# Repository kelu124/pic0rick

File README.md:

# the _pic0rick_ project

The pic0rick is a very central board for an ultrasound pulse-echo system. It is composed of a main board, based on the RP2040 (or RP2350) and easy to solder SMD, to which a single, and a double PMOD connector can connect to addons:

* The main board is equipped with a 60Msps, 10bit ADC. Front end is protected against high-voltage pulses, and features a proven time-gain compensation system consisting in a AD8331 (7.5 dB to 55.5dB) with a controlling (MCP4812) SPI DAC.
* The single PMOD connector can plug to the Pulser board, which can be equipped with a simple +-25V generation board. Together, they generate the pulse on behalf of the pic0rick main board. The setup can generate three-level pulses ( with a pair of MD1210 + TC6320 ).
* The double PMOD connector can be used for virtually anything. The current code allows for a VGA to be connected, which displays acquisitions from the board.

The current system uses both PIOs (one for the acquisition, the other for the VGA) which leaves the other resources of the rp2040 relatively free to use for your own priorities.

Published documents include:
* KiCad design files for the main board
* KiCad design files for the pulser + hv boards
* KiCad design files for the MUX
* KiCad design files for other boards =)
* rp2040/rp2350 firmware for the microcontroller.

I _know_ the PMODs aren't strictly speaking PMODs, I needed to have 5V facility on the header =)

And if you want to discuss the project - [meet us on our chat](https://matrix.to/#/!dEbJSiragnEvzVBdUa:matrix.org?via=matrix.org).

# Repository layout

| Path | Contents |
|------|----------|
| `firmware/` | The unified RP2040/RP2350 firmware (CMake project `adc-pulse`). One source tree with `-DMUX` / `-DDSP` build options. `hw/` = shared acquisition + pulser + spi1 DAC; `dsp/` = RP2350 DSP (CMSIS-DSP Hilbert envelope + binary protocol); `max/` = MAX14866 mux. `version.yaml` + `CHANGELOG.md` track the firmware version; `build.sh` builds all 6 variants into `dist/`. |
| `python/` | Host stack (`pic0rick` package): `device.py` (serial driver), `dsp.py` (binary frame protocol), `ndt_acquisition.py` (echo/thickness analysis + HDF5), and the `example_*.ipynb` notebooks. |
| `hardware/` | KiCad design files and `build.sh` fabrication outputs — main board (`adc/`), pulser + HV (`pulser/`), MUX (`mux/`), VGA (`vga/`), PSRAM (`psram/`). |
| `docs/` | Documentation: `dsp_output_formats.md`, `dsp_test_guide.md`, `images/`, `data/`, `fw_history/` (maintainer-curated reference `.uf2` baselines), and `claude/` (cross-session engineering notes). |
| `.github/workflows/` | CI: builds all firmware variants and publishes a release on push to `main`. |

# Getting Started

## Prerequisites

* pic0rick main board + pulser board + HV board (assembled)
* USB-C cable
* Python 3.9+
* A piezoelectric transducer (e.g. 5 MHz single-element contact probe)

## Building the firmware

The firmware is a single source tree (`firmware/`) with build options:

- **`-DMUX`** (default on) — MAX14866 HV multiplexer support.
- **`-DDSP`** (RP2350/`pico2` only) — on-board Hilbert-envelope DSP + binary
  protocol (see [DSP build](#dsp-build-rp2350) below).

```bash
cd firmware && ./build.sh          # builds all 6 variants into firmware/dist/:
#   rp2040-{mux,nomux}, rp2350-{mux,nomux}, rp2350-{mux,nomux}-dsp
```

Prebuilt `firmware/rp2040.uf2` / `firmware/rp2350.uf2` are the default (mux,
non-DSP) builds. CI publishes all variants as release assets.

## Flashing the firmware

1. Hold the **BOOTSEL** button on the RP2040/RP2350 while connecting USB — the board mounts as a USB mass-storage device. *(After the first flash you can instead send the `reboot-dfu` command over serial to re-enter the bootloader without the button.)*
2. Copy the compiled `.uf2` file into the drive. The board reboots automatically.
3. Verify: open a serial terminal at 115,200 baud. You should see the `run>` prompt (stdio build). Send `version` to confirm the firmware version, board and options.

## Installing the Python library

```bash
pip install pyserial numpy h5py scipy matplotlib
```

Clone this repo and add `python/` to your path, or run notebooks from the `python/` directory.

## Quick start

The examples below target the **DSP build** (`-DDSP`, RP2350) — the recommended
firmware, which streams CRC-checked binary frames. For the plain **stdio build**
see [Serial commands](#serial-commands-stdio--non-dsp-build).

```python
from pic0rick.device import Pic0rick
from pic0rick.ndt_acquisition import UltrasonicAcquisition

probe = Pic0rick()           # auto-detects the USB serial port
print(probe.version()['raw'])

# Set TGC gain (raw DAC value 0–1023; higher = more gain)
probe.set_gain(300)

# Configure and arm the pulser so the capture transmits
probe.configure_pulse(negative_ns=200, damp_ns=2000, positive_ns=200,
                      order="pos-first")
probe.arm_pulser()

frame = probe.read_raw()     # 8000-sample raw ADC frame (CRC-checked)
signal = frame.samples()     # numpy uint16, 0..1023
# envelope = probe.read_fft().samples()   # 4096-sample Hilbert envelope
probe.disarm_pulser()
```

> On the **stdio (non-DSP)** build instead use `probe.dac(gain)`,
> `probe.pulse_adc_trigger(pon, poff, damp)`, `probe.read()`.

Or use the higher-level acquisition wrapper (drives the DSP build for you):

```python
acq = UltrasonicAcquisition.from_probe(
    Fech=60e6,
    pon=70,        # pulse-on duration [ns]
    poff=70,       # pulse-off duration [ns]
    damp=6000,     # damping duration [ns]
    gain=300,      # raw DAC value (0–1023)
    target="1018 steel 25 mm",
    h5_path="my_scan.h5",
)
acq.plot()
```

## Serial commands (stdio / non-DSP build)

The stdio build exposes a text protocol at 115,200 baud (USB CDC), with a `run>`
prompt:

| Command | Arguments | Description |
|---------|-----------|-------------|
| `start acq <pon> <poff> <damp>` | nanoseconds | Fire pulse, DMA-capture 8000 samples |
| `write dac <N>` | 0–1023 | Set TGC gain (MCP4812 10-bit DAC) |
| `read` | — | Return last captured buffer (hex, comma-separated 10-bit values) |
| `write mux <hex>` | hex word | Write the MAX14866 shift register *(MUX builds)* |
| `set mux` / `clear mux` | — | Pulse the MAX14866 SET / CLR line *(MUX builds)* |
| `version` | — | Print firmware version, board/chip, options, git hash, release URL |
| `reboot-dfu` | — | Reboot into the USB bootloader (BOOTSEL) for reflashing |

> The **DSP build** uses different commands (`dac write`, `read_raw`, `read_fft`,
> …) and a binary protocol — see [DSP build](#dsp-build-rp2350).

### Parameter details

**`pon` / `poff` / `damp`** — expressed in **nanoseconds** from Python. The firmware converts them to 125 MHz clock cycles internally (divides by 8).

**`gain`** — raw 10-bit DAC value (0–1023) controlling the VGAIN pin of the AD8331 TGC amplifier (7.5 dB to 55.5 dB range). The example notebook uses values in the 0–500 range.

### DSP build (RP2350)

Building with `-DDSP=ON` (RP2350/`pico2`) adds an on-board DSP path: a float32
CMSIS-DSP Hilbert envelope. Instead of the text REPL it speaks a binary framed
protocol (64-byte header + CRC32) with two capture modes:

- **`read_raw`** — 8000 raw ADC samples (no FFT).
- **`read_fft`** — 4096-sample Hilbert envelope.

plus `acq raw|envelope|alaw`, `stream start|stop`, `dsp scale|selftest`,
`dac write <0..1023>`, `pulse config <neg_ns> <damp_ns> <pos_ns> <neg-first|pos-first>`,
`pulser arm|disarm`, `status`, `help`, `version`, `reboot-dfu`.

Drive it from Python with `pic0rick.dsp` and these `Pic0rick` methods:
`version()`, `status()`, `set_gain(n)`, `configure_pulse(...)`,
`arm_pulser()`/`disarm_pulser()`, `read_raw()`, `read_fft()`, `capture(payload)`.
The frame and status formats are documented in
[`docs/dsp_output_formats.md`](docs/dsp_output_formats.md); see
[`docs/dsp_test_guide.md`](docs/dsp_test_guide.md) and the
`python/example_dsp.ipynb` / `python/example_simple.ipynb` notebooks.

## Signal chain

```
Transducer
   │
   ├──► TX path: PIO pulser GPIO11/12 (P+/P-) + GPIO16/17 (PDAMP/OE) → MD1213 + TC6320 → ±25V three-level pulse
   │
   └──► RX path: T/R protection → AD8331 TGC (gain set by MCP4812 DAC)
                  → 60 Msps 10-bit ADC (PIO + DMA, 8000 samples/acquisition)
                  → USB CDC → Python
```

The ADC samples are 10-bit unsigned (0–1023, mid-scale = 512). The `ndt_acquisition` wrapper normalises them to float32 in the range ≈ [−1, 1]:

```python
signal = (adc_count - 512) / 512.0
```

# Setup

## The three boards assemble look like this

## Example of acquisitions

## Demo of output to VGA 

Beware. This is not a standard development, more of a proof of concept. It lives on a [separate branch here](https://github.com/kelu124/pic0rick/tree/VGA).

Only using the pico to setup gain and trigger acquisitions. The screen displays the gain value (0 to 9, with a 100x divider). Displays raw buffer of acquisition.

## Example of a compact assembly 

Within a game card footprint

# Along with the other boards

# Assembly

## What you get :

## Before assembly

You will need to get a few headers, a raspberry pico, and SMA connectors

## Focus on the Pulser connector

## Once assembled

### Top view

### Bottom view 

# License

This work is based on three previous TAPR projects, [the echOmods project](https://github.com/kelu124/echomods/), the [un0rick project](https://doi.org/10.5281/zenodo.377054), and the [lit3rick project](https://doi.org/10.5281/zenodo.5792245) - their boards are open hardware and software, developped with open-source elements as much as possible.

Copyright Luc Jonveaux (<kelu124@gmail.com>) 2024

* The hardware is licensed under TAPR Open Hardware License (<www.tapr.org/OHL>)
* The software components are free software: you can redistribute it and/or modify it under the terms of the GNU General Public License as published by the Free Software Foundation, either version 3 of the License, or (at your option) any later version.
* The docs is licensed under a [Creative Commons Attribution-ShareAlike 3.0 Unported License](http://creativecommons.org/licenses/by-sa/3.0/).

## Disclaimer

This project is distributed WITHOUT ANY EXPRESS OR IMPLIED WARRANTY, INCLUDING OF MERCHANTABILITY, SATISFACTORY QUALITY AND FITNESS FOR A PARTICULAR PURPOSE.

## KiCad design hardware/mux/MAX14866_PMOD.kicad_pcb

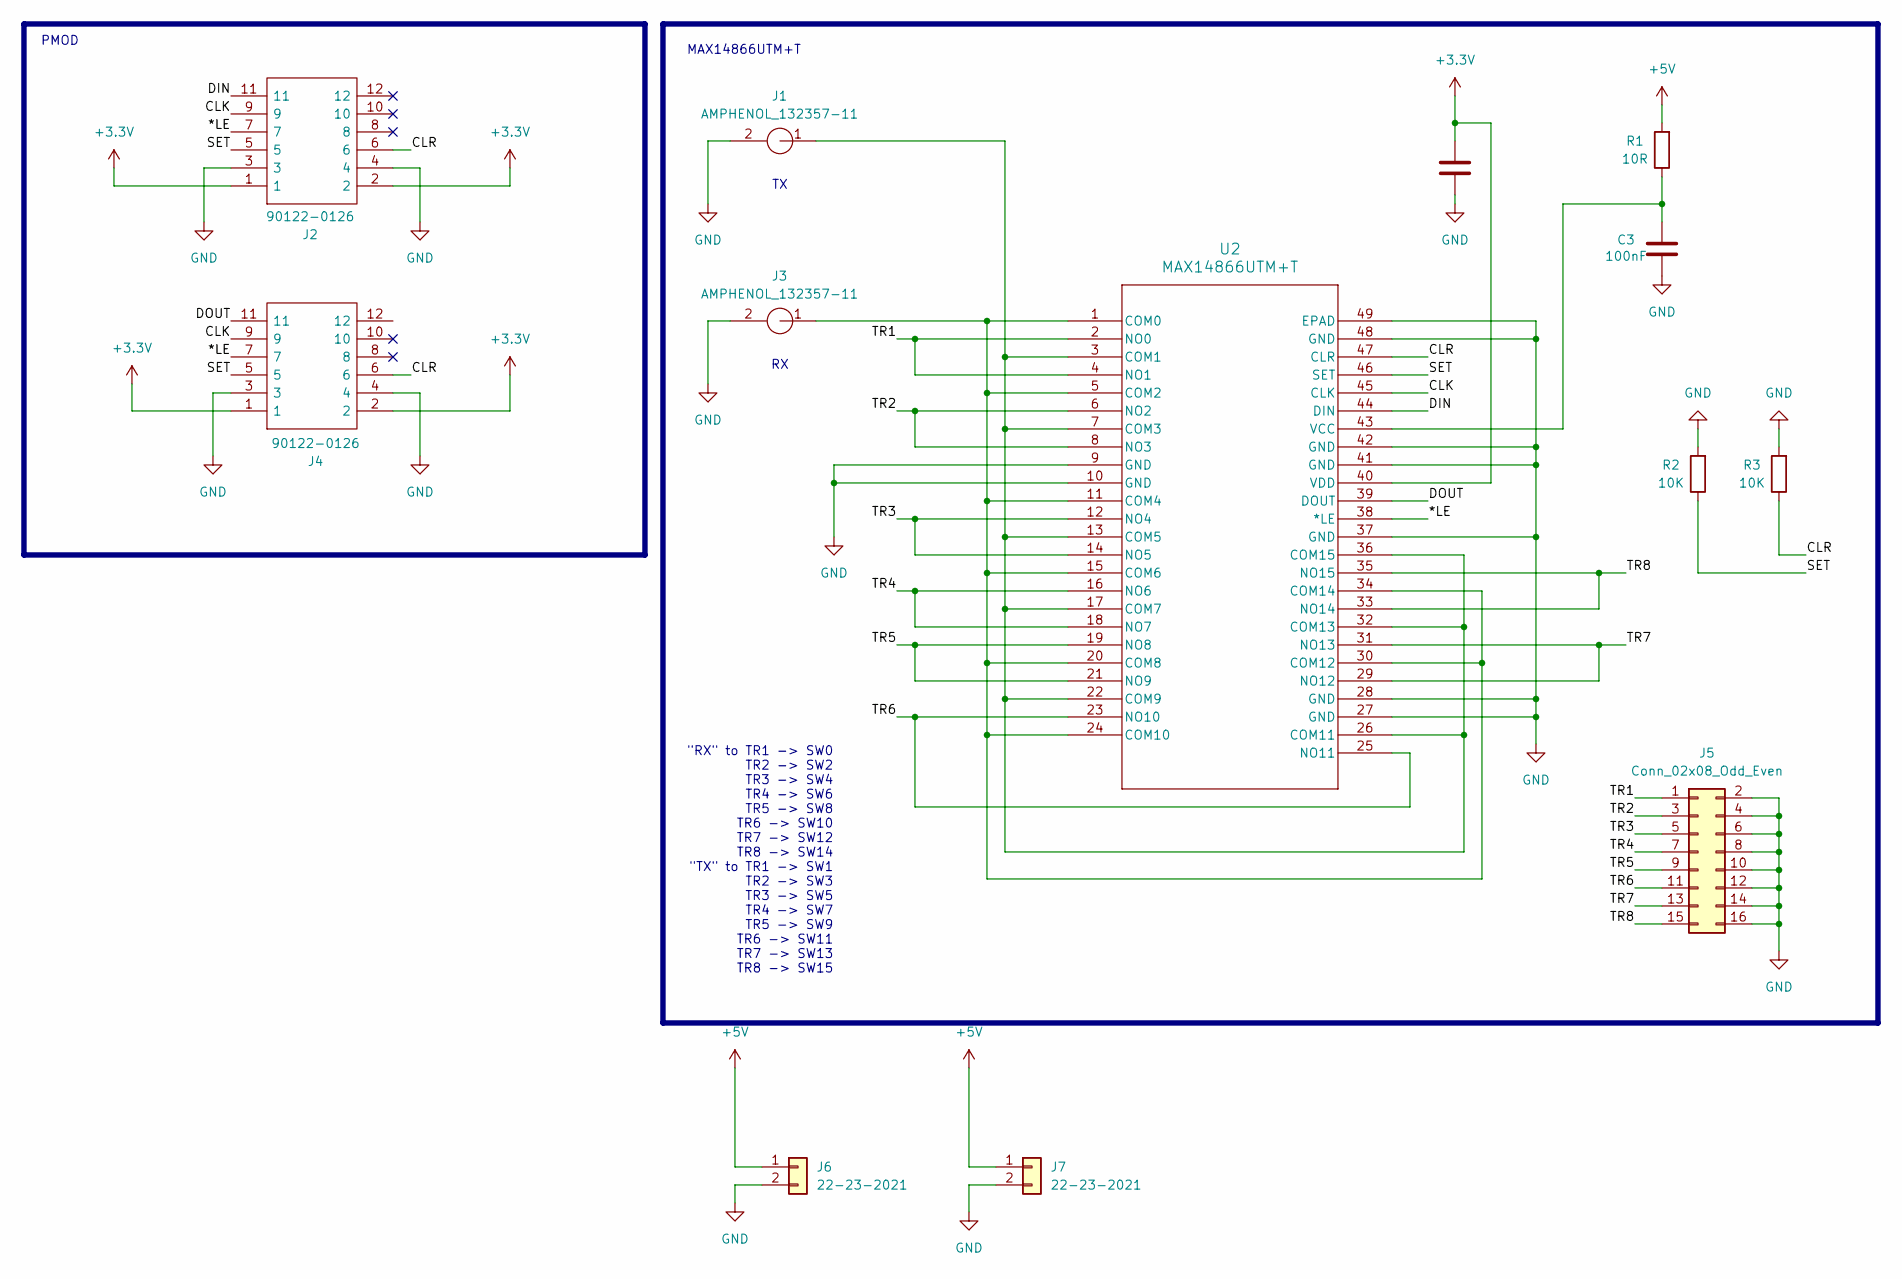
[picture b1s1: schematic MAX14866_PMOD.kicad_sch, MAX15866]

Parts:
C2: 1uF; C_1206_3216Metric
C3: 100nF; C_1206_3216Metric
J1, J3: AMPHENOL_132357-11; AMPHENOL_132357-11-MOD; Mouser Part Number 530-142-0701-801
J2: 90122-0126; PinHeader_2x06_P2.54mm_Horizontal; Mouser Part Number 710-613012243121
J4: 90122-0126; PinSocket_2x06_P2.54mm_Horizontal; Mouser Part Number 710-613012243121
J5: Conn_02x08_Odd_Even; PinHeader_2x08_P2.54mm_Vertical
J6: 22-23-2021; PinSocket_2x01_P2.54mm_Horizontal; MPN 22-23-2021
J7: 22-23-2021; PinHeader_2x01_P2.54mm_Horizontal; MPN 22-23-2021
R1: 10R; R_1206_3216Metric
R2, R3: 10K; R_1206_3216Metric
U2: MAX14866UTM+T; 21-0144H_T4877-6_MXM

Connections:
+3.3V: C2.2, J2.1, J2.2, J4.1, J4.2, U2.40 (VDD)
+5V: J6.1, J7.1, R1.2
/*LE: J2.7, J4.7, U2.38 (*LE)
/CLK: J2.9, J4.9, U2.45 (CLK)
/CLR: J2.6, J4.6, R3.1, U2.47 (CLR)
/DIN: J2.11, U2.44 (DIN)
/DOUT: J4.11, U2.39 (DOUT)
/SET: J2.5, J4.5, R2.1, U2.46 (SET)
/TR1: J5.1, U2.2 (NO0), U2.4 (NO1)
/TR2: J5.3, U2.6 (NO2), U2.8 (NO3)
/TR3: J5.5, U2.12 (NO4), U2.14 (NO5)
/TR4: J5.7, U2.16 (NO6), U2.18 (NO7)
/TR5: J5.9, U2.19 (NO8), U2.21 (NO9)
/TR6: J5.11, U2.23 (NO10), U2.25 (NO11)
/TR7: J5.13, U2.29 (NO12), U2.31 (NO13)
/TR8: J5.15, U2.33 (NO14), U2.35 (NO15)
GND: C2.1, C3.1, J1.2, J2.3, J2.4, J3.2, J4.3, J4.4, J5.2, J5.4, J5.6, J5.8, J5.10, J5.12, J5.14, J5.16, J6.2, J7.2, R2.2, R3.2, U2.9 (GND), U2.10 (GND), U2.27 (GND), U2.28 (GND), U2.37 (GND), U2.41 (GND), U2.42 (GND), U2.48 (GND), U2.49 (EPAD)
unnamed: J3.1, U2.1 (COM0), U2.5 (COM2), U2.11 (COM4), U2.15 (COM6), U2.20 (COM8), U2.24 (COM10), U2.30 (COM12), U2.34 (COM14)
unnamed: J1.1, U2.3 (COM1), U2.7 (COM3), U2.13 (COM5), U2.17 (COM7), U2.22 (COM9), U2.26 (COM11), U2.32 (COM13), U2.36 (COM15)
unnamed: C3.2, R1.1, U2.43 (VCC)

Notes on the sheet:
PMOD
MAX14866UTM+T
"RX" to TR1 -> SW0 TR2 -> SW2 TR3 -> SW4 TR4 -> SW6 TR5 -> SW8 TR6 -> SW10 TR7 -> SW12 TR8 -> SW14 "TX" to TR1 -> SW1 TR2 -> SW3 TR3 -> SW5 TR4 -> SW7 TR5 -> SW9 TR6 -> SW11 TR7 -> SW13 TR8 -> SW15

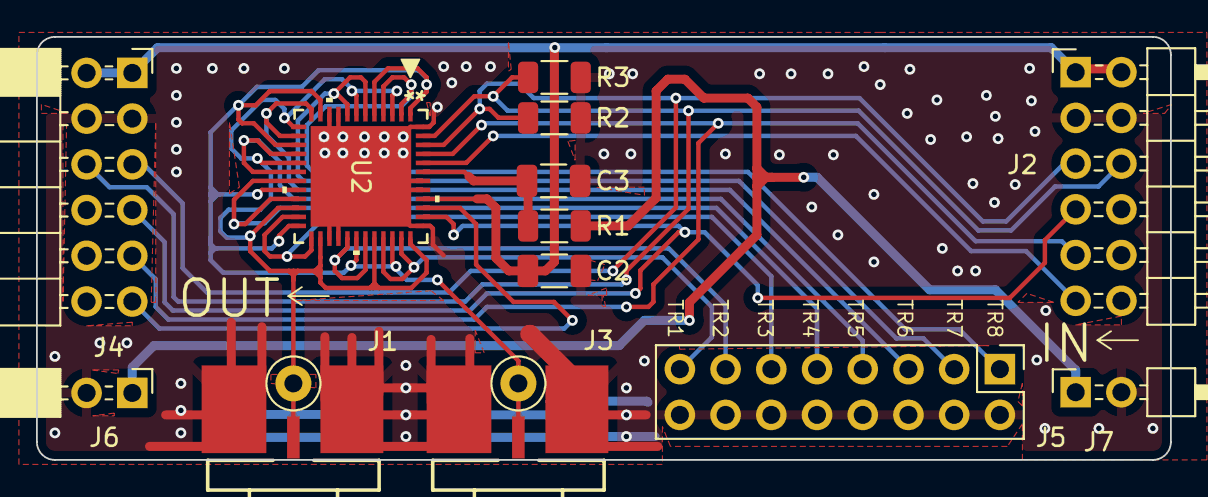
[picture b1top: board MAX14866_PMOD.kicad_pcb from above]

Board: 2 copper layers, 63.0 x 23.5 mm, 13 parts (0 on the bottom side), 20 nets.

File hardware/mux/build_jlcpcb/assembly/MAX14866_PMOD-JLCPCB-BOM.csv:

"Comment","Designator","Footprint","MPN","Manufacturer","LCSC Part #"
"100nF","C3","C_1206_3216Metric","","",""
"1uF","C2","C_1206_3216Metric","","",""
"22-23-2021","J6","PinSocket_2x01_P2.54mm_Horizontal","22-23-2021","",""
"22-23-2021","J7","PinHeader_2x01_P2.54mm_Horizontal","22-23-2021","",""
"90122-0126","J2","PinHeader_2x06_P2.54mm_Horizontal","90122-0126","",""
"90122-0126","J4","PinSocket_2x06_P2.54mm_Horizontal","90122-0126","",""
"AMPHENOL_132357-11","J1,J3","AMPHENOL_132357-11-MOD","AMPHENOL_132357-11","",""
"Conn_02x08_Odd_Even","J5","PinHeader_2x08_P2.54mm_Vertical","","",""
"10R","R1","R_1206_3216Metric","","",""
"10K","R2,R3","R_1206_3216Metric","","",""
"MAX14866UTM+T","U2","21-0144H_T4877-6_MXM","","",""

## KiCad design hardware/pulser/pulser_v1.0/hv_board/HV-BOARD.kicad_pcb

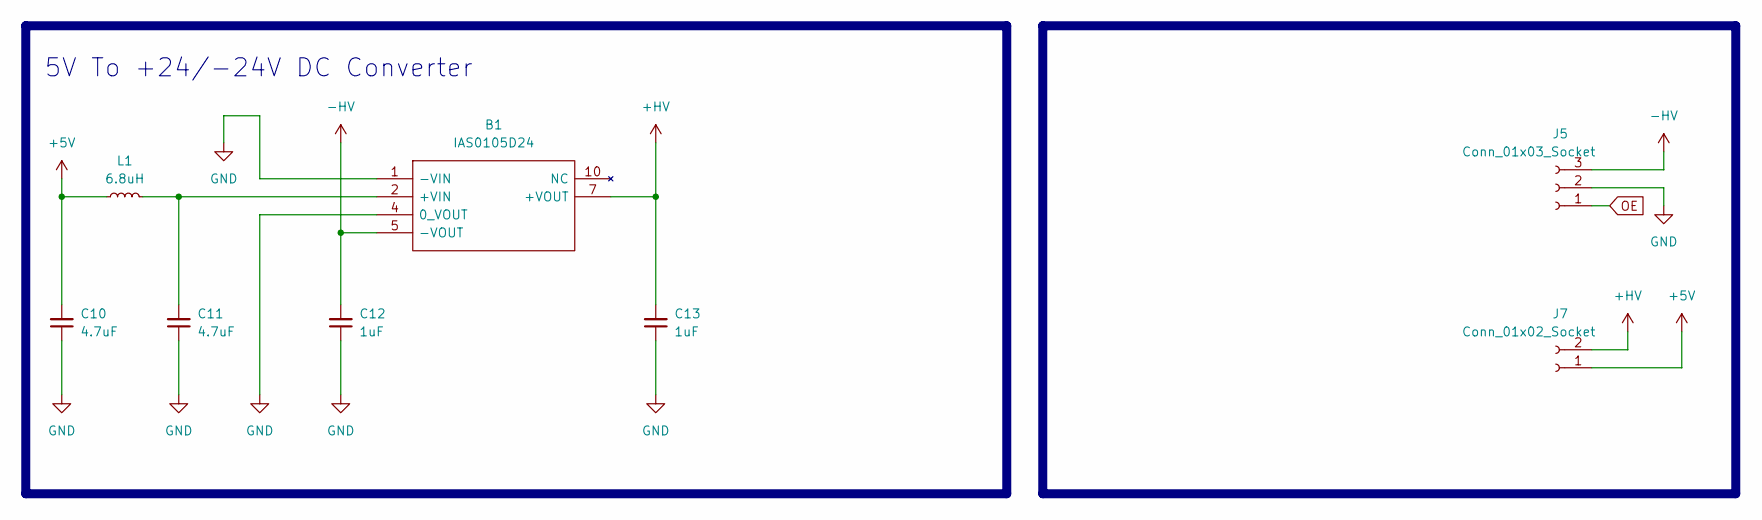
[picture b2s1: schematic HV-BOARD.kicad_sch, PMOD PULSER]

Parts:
B1: IAS0105D24; Mouser Part Number 209-IAS0105D09
C10, C11: 4.7uF; C_1206_3216Metric
C12, C13: 1uF; C_1206_3216Metric
J5: Conn_01x03_Socket; PinSocket_1x03_P2.54mm_Vertical
J7: Conn_01x02_Socket; PinSocket_1x02_P2.54mm_Vertical
L1: 6.8uH; L_1206_3216Metric; MPN ILSB1206ER6R8K

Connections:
+5V: C10.2, J7.1, L1.1
+HV: B1.7 (+VOUT), C13.2, J7.2
-HV: B1.5 (-VOUT), C12.2, J5.3
GND: B1.1 (-VIN), B1.4 (0_VOUT), C10.1, C11.1, C12.1, C13.1, J5.2
unnamed: B1.2 (+VIN), C11.2, L1.2
OE: J5.1

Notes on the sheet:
5V To +24/-24V DC Converter

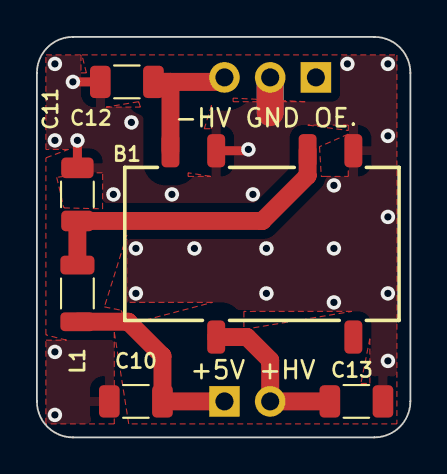
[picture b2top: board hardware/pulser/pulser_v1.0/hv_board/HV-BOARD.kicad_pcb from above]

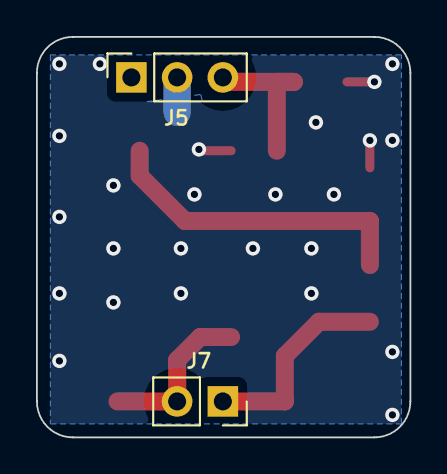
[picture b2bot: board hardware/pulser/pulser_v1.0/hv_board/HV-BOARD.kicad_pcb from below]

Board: 2 copper layers, 20.7 x 22.2 mm, 8 parts (2 on the bottom side), 5 nets.

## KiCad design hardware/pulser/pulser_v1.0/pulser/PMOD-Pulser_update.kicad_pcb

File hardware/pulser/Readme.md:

# Pulser hardware file

This folder contains the newest version of pulser and HV board, with breakbout

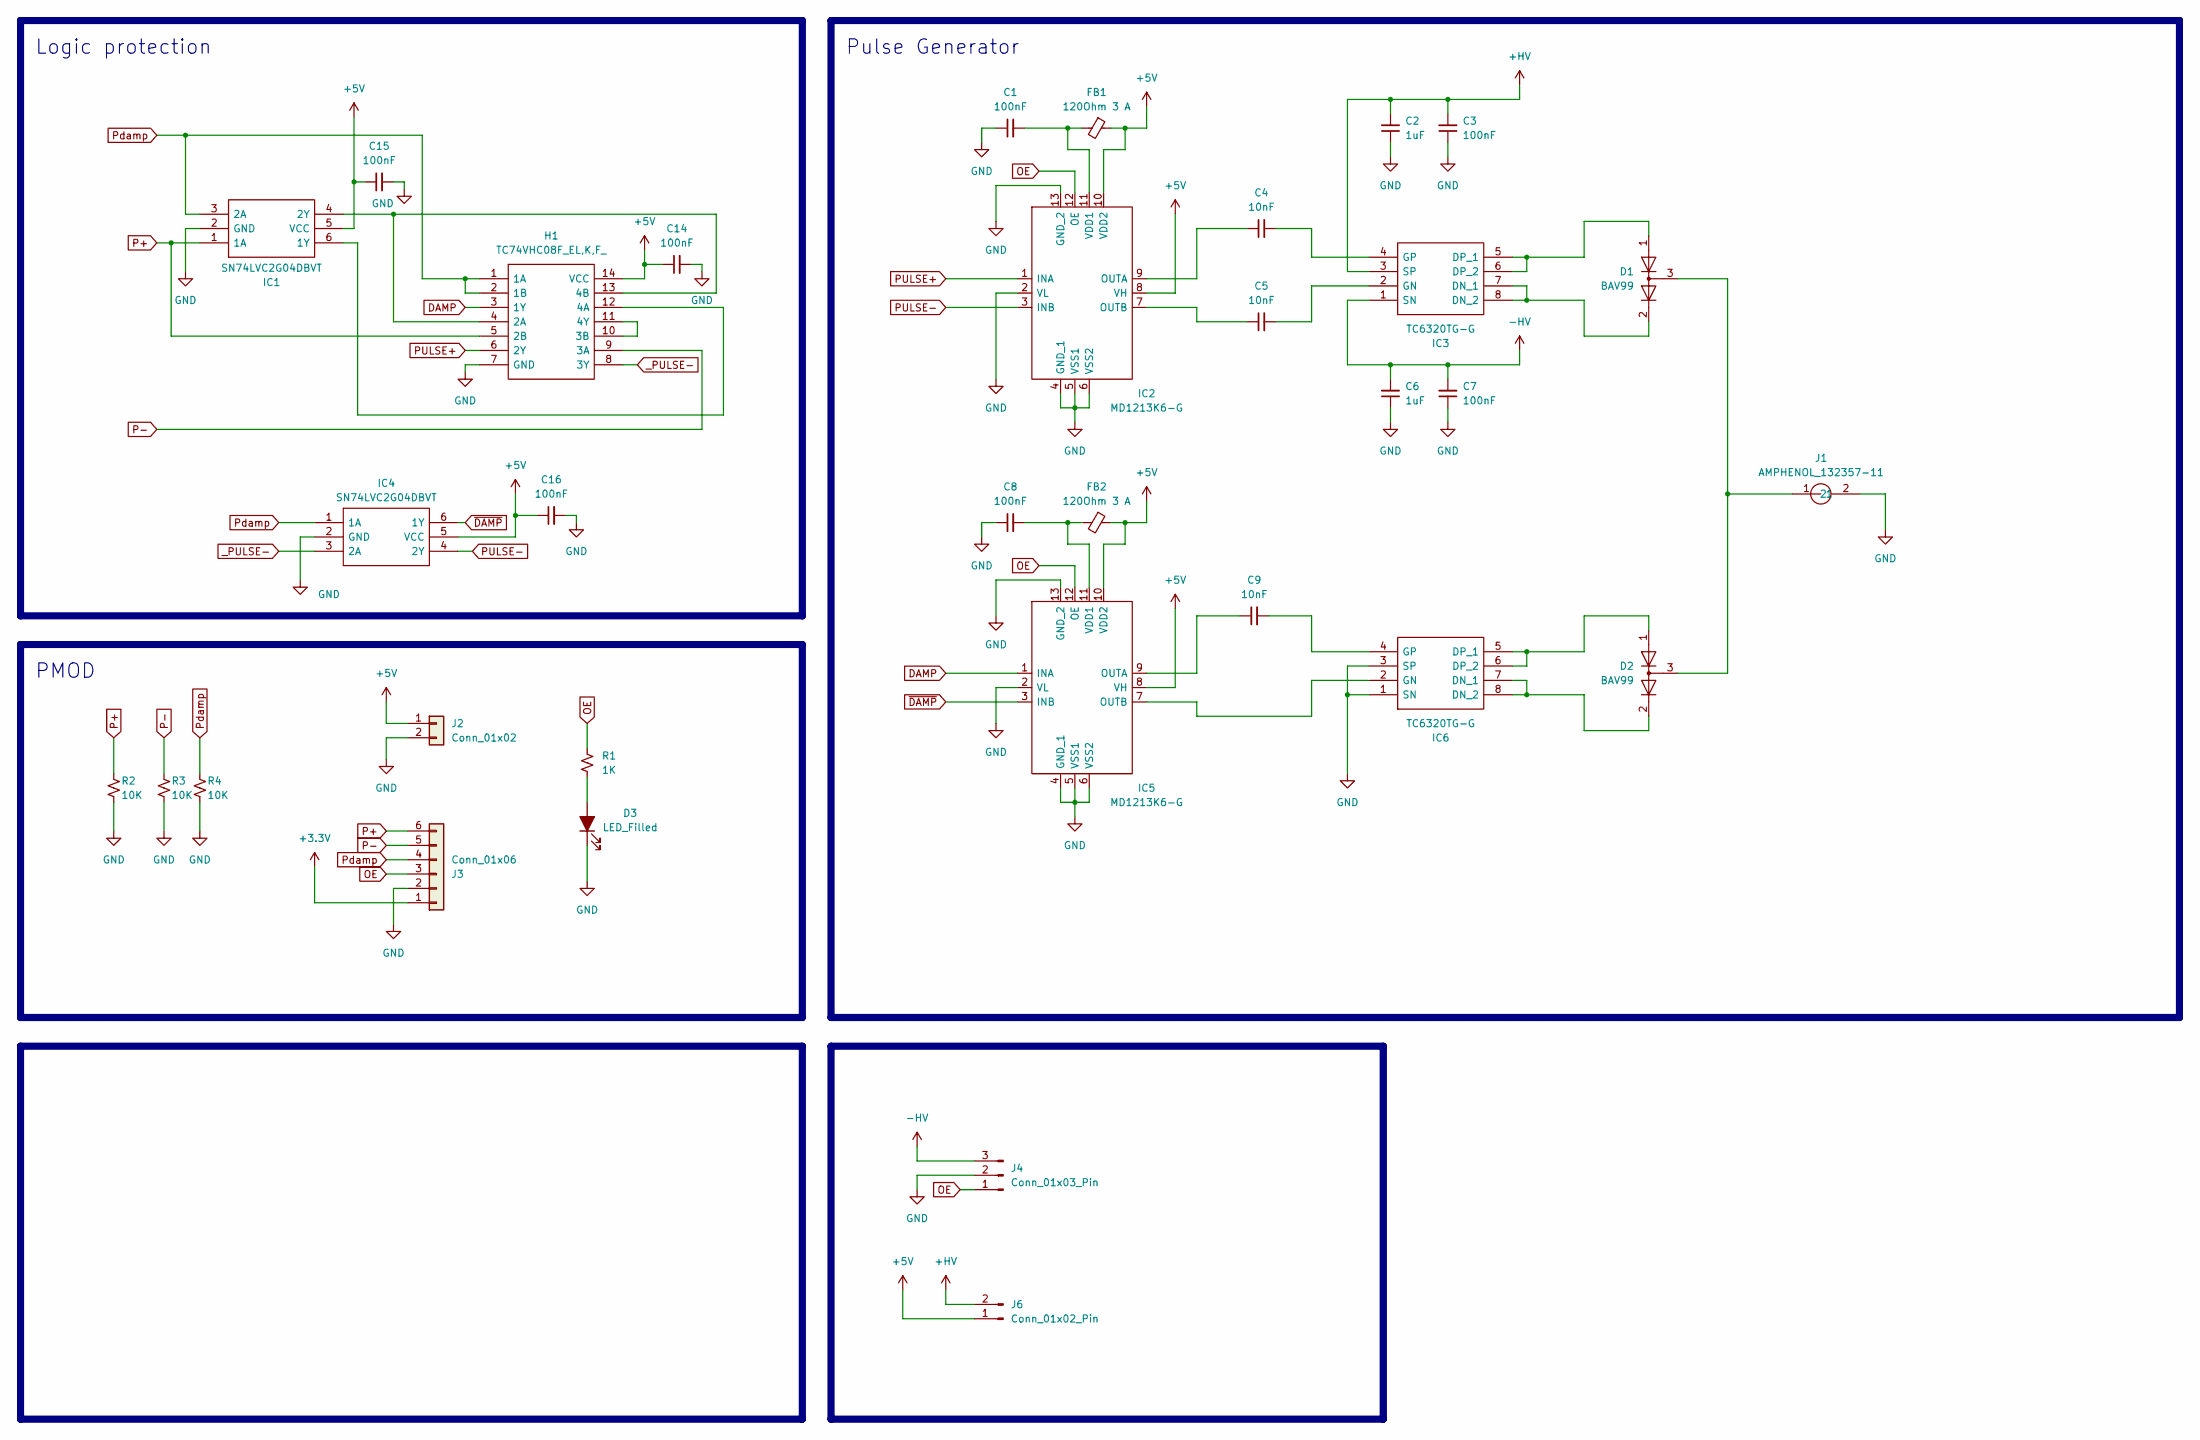
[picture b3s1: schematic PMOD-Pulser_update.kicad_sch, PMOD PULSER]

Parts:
C1, C3, C7, C8, C14, C15, C16: 100nF; C_1206_3216Metric
C2, C6: 1uF; C_1206_3216Metric
C4, C5, C9: 10nF; C_1206_3216Metric
D1, D2: BAV99; SOT-23; MPN BAV99
D3: LED_Filled; D_0805_2012Metric
FB1, FB2: 120Ohm 3 A; L_1206_3216Metric; MPN 742792113
H1: TC74VHC08F_EL,K,F_; SOIC127P780X190-14N; Mouser Part Number 757-TC74VHC08FELKF
IC1, IC4: SN74LVC2G04DBVT; SN74LVC2G04DBV; Mouser Part Number 595-SN74LVC2G04DBVT
IC2, IC5: MD1213K6-G; MD1213; Mouser Part Number 689-MD1213K6-G
IC3, IC6: TC6320TG-G; SOIC127P600X175-8N; Mouser Part Number 689-TC6320TG-G
J1: AMPHENOL_132357-11; Mouser Part Number 530-142-0701-801
J2: Conn_01x02; PinHeader_2x01_P2.54mm_Horizontal
J3: Conn_01x06; PinHeader_1x06_P2.54mm_Horizontal
J4: Conn_01x03_Pin; PinHeader_1x03_P2.54mm_Vertical
J6: Conn_01x02_Pin; PinHeader_1x02_P2.54mm_Vertical
R1: 1K; R_1206_3216Metric
R2, R3, R4: 10K; R_1206_3216Metric

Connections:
+3.3V: J3.1
+5V: C14.1, C15.1, C16.1, FB1.1, FB2.1, H1.14 (VCC), IC1.5 (VCC), IC2.8 (VH), IC2.10 (VDD2), IC4.5 (VCC), IC5.8 (VH), IC5.10 (VDD2), J2.1, J6.1
+HV: C2.2, C3.2, IC3.3 (SP), J6.2
-HV: C6.2, C7.2, IC3.1 (SN), J4.3
DAMP: H1.3 (1Y), IC5.1 (INA)
GND: C1.1, C2.1, C3.1, C6.1, C7.1, C8.1, C14.2, C15.2, C16.2, D3.1 (K), H1.7 (GND), IC1.2 (GND), IC2.2 (VL), IC2.4 (GND_1), IC2.5 (VSS1), IC2.6 (VSS2), IC2.13 (GND_2), IC4.2 (GND), IC5.2 (VL), IC5.4 (GND_1), IC5.5 (VSS1), IC5.6 (VSS2), IC5.13 (GND_2), IC6.1 (SN), IC6.3 (SP), J1.2, J2.2, J3.2, J4.2, R2.2, R3.2, R4.2
unnamed: D1.2 (A), IC3.7 (DN_1), IC3.8 (DN_2)
unnamed: D1.3 (K), D2.3 (K), J1.1
unnamed: D2.2 (A), IC6.7 (DN_1), IC6.8 (DN_2)
unnamed: D3.2 (A), R1.2
unnamed: H1.4 (2A), H1.13 (4B), IC1.4 (2Y)
unnamed: H1.10 (3B), H1.11 (4Y)
unnamed: H1.12 (4A), IC1.6 (1Y)
unnamed: C4.1, IC2.9 (OUTA)
unnamed: C5.1, IC2.7 (OUTB)
unnamed: C1.2, FB1.2, IC2.11 (VDD1)
unnamed: D1.1 (K), IC3.5 (DP_1), IC3.6 (DP_2)
unnamed: C5.2, IC3.2 (GN)
unnamed: C4.2, IC3.4 (GP)
unnamed: C9.1, IC5.9 (OUTA)
unnamed: IC5.7 (OUTB), IC6.2 (GN)
unnamed: C8.2, FB2.2, IC5.11 (VDD1)
unnamed: D2.1 (K), IC6.5 (DP_1), IC6.6 (DP_2)
unnamed: C9.2, IC6.4 (GP)
OE: IC2.12 (OE), IC5.12 (OE), J3.3, J4.1, R1.1
P+: H1.5 (2B), IC1.1 (1A), J3.6, R2.1
P-: H1.9 (3A), J3.5, R3.1
PULSE+: H1.6 (2Y), IC2.1 (INA)
PULSE-: IC2.3 (INB), IC4.4 (2Y)
Pdamp: H1.1 (1A), H1.2 (1B), IC1.3 (2A), IC4.1 (1A), J3.4, R4.1
_PULSE-: H1.8 (3Y), IC4.3 (2A)
~DAMP: IC4.6 (1Y), IC5.3 (INB)

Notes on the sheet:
PMOD
Logic protection
Pulse Generator

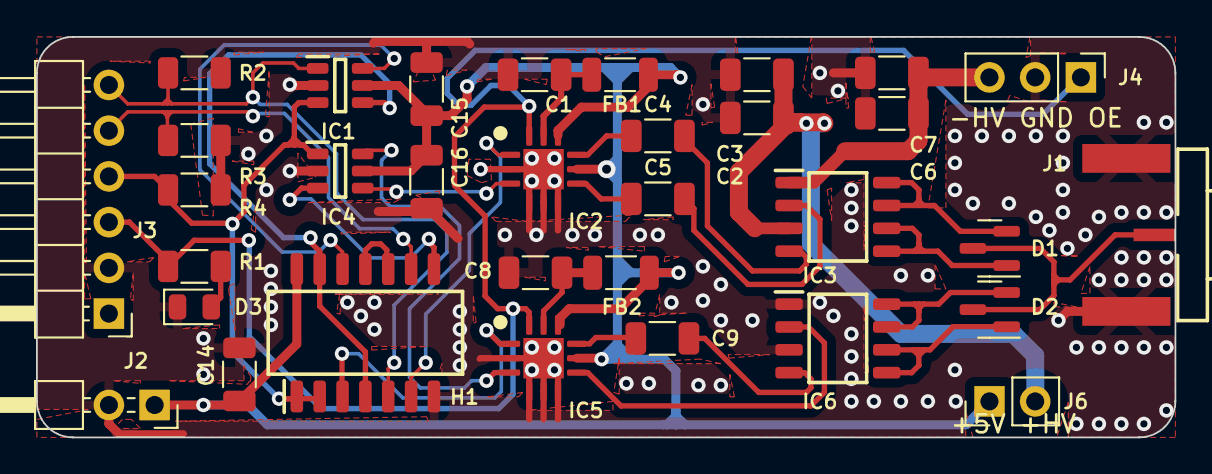
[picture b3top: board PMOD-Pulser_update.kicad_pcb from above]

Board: 2 copper layers, 63.2 x 22.2 mm, 33 parts (0 on the bottom side), 31 nets.

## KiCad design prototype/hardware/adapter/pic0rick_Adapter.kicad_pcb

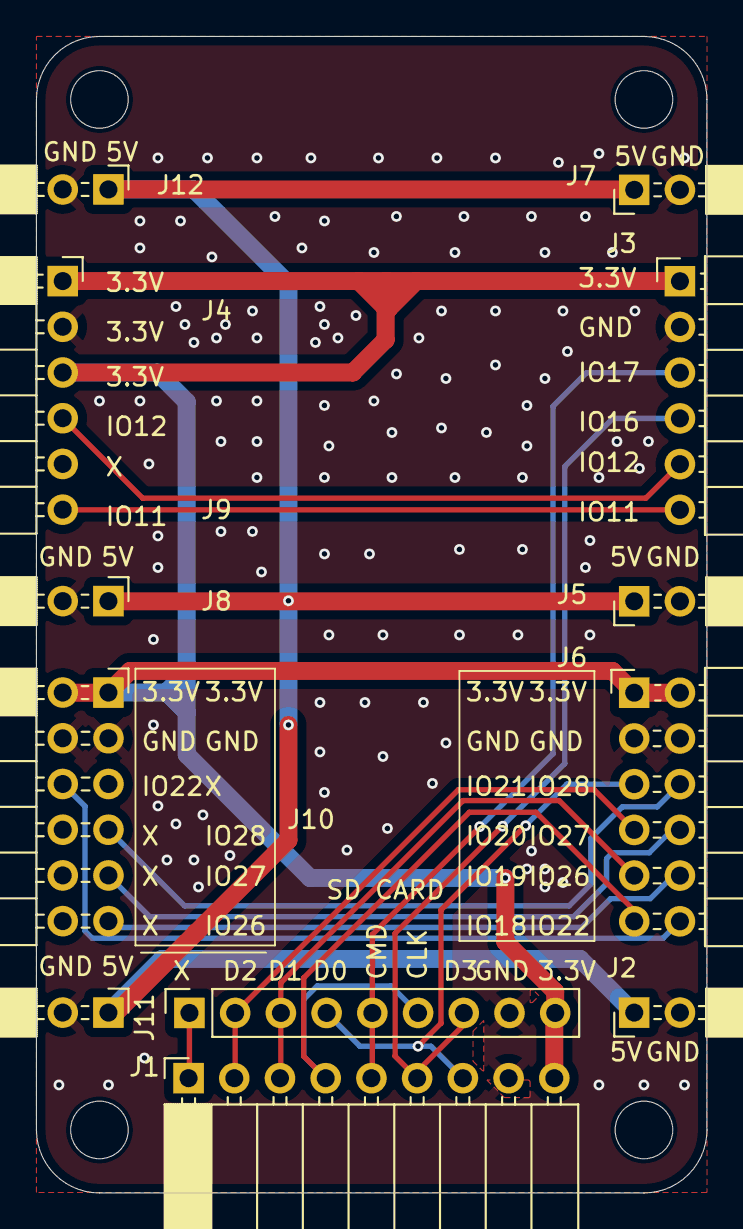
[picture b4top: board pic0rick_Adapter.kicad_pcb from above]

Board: 2 copper layers, 37.2 x 64.2 mm, 12 parts (0 on the bottom side), 15 nets.

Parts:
J1: Conn_01x09_Socket; PinSocket_1x09_P2.54mm_Horizontal
J2, J5, J7, J9, J10, J12: Conn_01x02_Socket; PinSocket_2x01_P2.54mm_Horizontal
J3: Conn_01x06_Pin; PinHeader_1x06_P2.54mm_Horizontal
J4: Conn_01x06_Socket; PinSocket_1x06_P2.54mm_Horizontal
J6: Conn_02x06_Odd_Even; PinHeader_2x06_P2.54mm_Horizontal
J8: Conn_02x06_Odd_Even; PinSocket_2x06_P2.54mm_Horizontal
J11: Conn_01x09_Socket; PinSocket_1x09_P2.54mm_Vertical

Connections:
+3.3V: J1.9, J3.1, J4.1, J4.3, J6.1, J6.2, J8.1, J8.2, J11.9
+5V: J2.1, J5.1, J7.1, J9.1, J10.1, J12.1
GND: J1.8, J2.2, J3.2, J4.2, J5.2, J6.3, J6.4, J7.2, J8.3, J8.4, J9.2, J10.2, J11.8, J12.2
GPIO11: J3.6, J4.6
GPIO12: J3.5, J4.4
GPIO16: J1.6, J3.4, J11.7
GPIO17: J1.5, J3.3, J11.5
GPIO18: J1.4, J6.11, J11.6
GPIO19: J1.3, J6.9, J11.3
GPIO20: J1.2, J6.7, J11.2
GPIO21: J1.7, J6.5, J11.4
GPIO22: J6.12, J8.6
GPIO26: J6.10, J8.11
GPIO27: J6.8, J8.9
GPIO28: J6.6, J8.7

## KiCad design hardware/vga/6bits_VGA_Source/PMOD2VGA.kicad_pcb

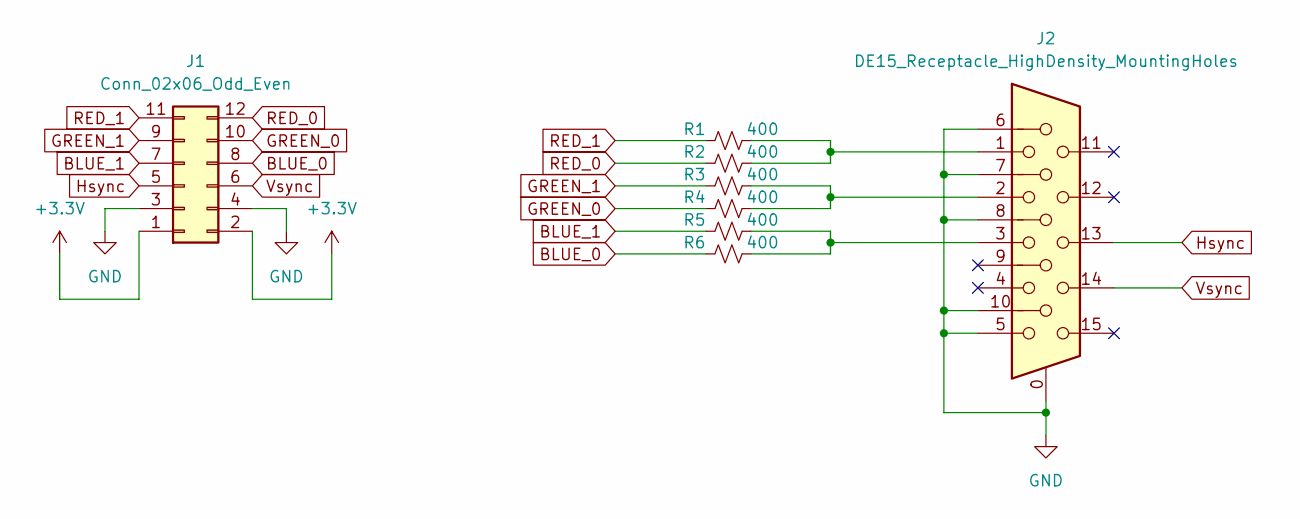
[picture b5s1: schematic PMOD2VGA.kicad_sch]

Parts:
J1: Conn_02x06_Odd_Even; PinHeader_2x06_P2.54mm_Horizontal
J2: DE15_Receptacle_HighDensity_MountingHoles; DSUB-15-HD_Female_Horizontal_P2.29x1.98mm_EdgePinOffset3.03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
R1, R2, R3, R4, R5, R6: 400; R_1206_3216Metric

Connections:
+3.3V: J1.1, J1.2
BLUE_0: J1.8, R6.1
BLUE_1: J1.7, R5.1
GND: J1.3, J1.4, J2.0, J2.5, J2.6, J2.7, J2.8, J2.10
GREEN_0: J1.10, R4.1
GREEN_1: J1.9, R3.1
Hsync: J1.5, J2.13
unnamed: J2.1, R1.2, R2.2
unnamed: J2.2, R3.2, R4.2
unnamed: J2.3, R5.2, R6.2
RED_0: J1.12, R2.1
RED_1: J1.11, R1.1
Vsync: J1.6, J2.14

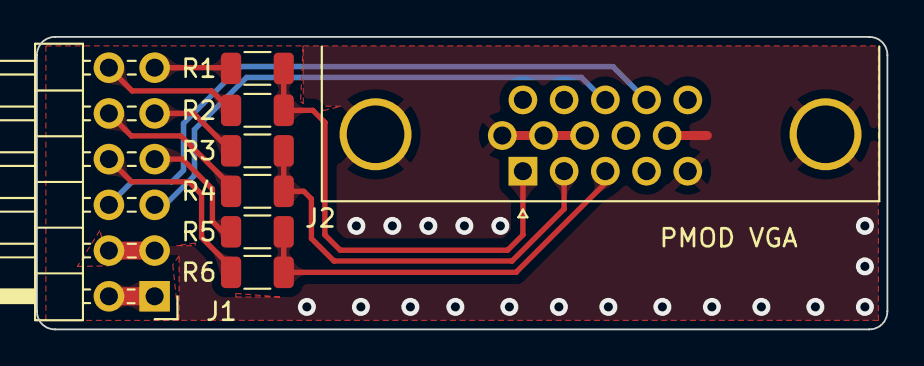
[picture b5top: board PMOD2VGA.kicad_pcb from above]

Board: 2 copper layers, 47.2 x 16.2 mm, 8 parts (0 on the bottom side), 13 nets.

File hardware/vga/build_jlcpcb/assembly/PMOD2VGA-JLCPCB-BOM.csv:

"Comment","Designator","Footprint","MPN","Manufacturer","LCSC Part #"
"Conn_02x06_Odd_Even","J1","PinHeader_2x06_P2.54mm_Horizontal","","",""
"DE15_Receptacle_HighDensity_MountingHoles","J2","DSUB-15-HD_Female_Horizontal_P2.29x1.98mm_EdgePinOffset3.03mm_Housed_MountingHolesOffset4.94mm","","",""
"400","R1,R2,R3,R4,R5,R6","R_1206_3216Metric","","",""

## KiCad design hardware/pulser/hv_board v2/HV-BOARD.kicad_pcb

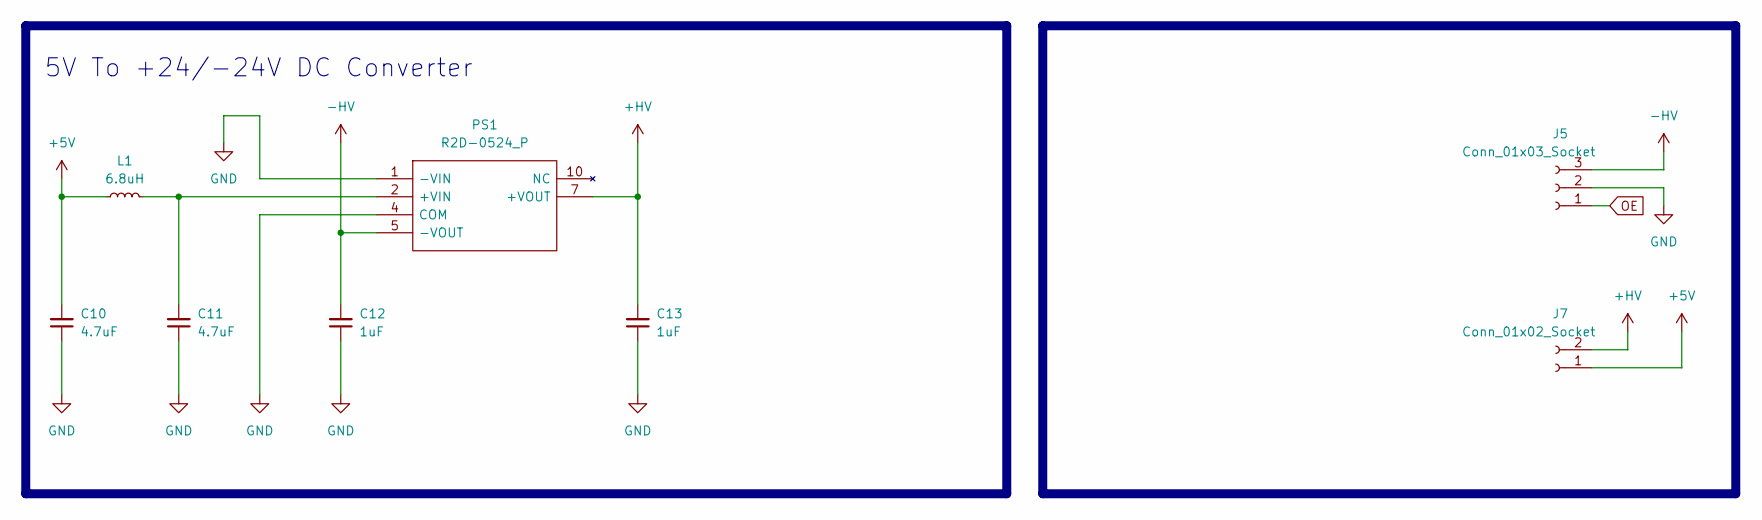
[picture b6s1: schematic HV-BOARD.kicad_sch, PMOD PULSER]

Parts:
C10, C11: 4.7uF; C_1206_3216Metric
C12, C13: 1uF; C_1206_3216Metric
J5: Conn_01x03_Socket; PinSocket_1x03_P2.54mm_Vertical
J7: Conn_01x02_Socket; PinSocket_1x02_P2.54mm_Vertical
L1: 6.8uH; L_1206_3216Metric; MPN ILSB1206ER6R8K
PS1: R2D-0524_P; R2D0524P; Mouser Part Number 919-R2D-0524P

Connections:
+5V: C10.2, J7.1, L1.1
+HV: C13.2, J7.2, PS1.7 (+VOUT)
-HV: C12.2, J5.3, PS1.5 (-VOUT)
GND: C10.1, C11.1, C12.1, C13.1, J5.2, PS1.1 (-VIN), PS1.4 (COM)
unnamed: C11.2, L1.2, PS1.2 (+VIN)
OE: J5.1

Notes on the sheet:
5V To +24/-24V DC Converter

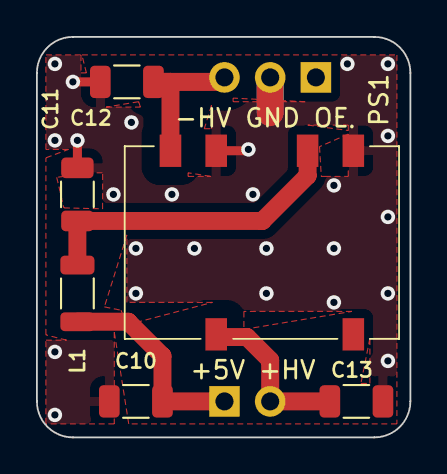
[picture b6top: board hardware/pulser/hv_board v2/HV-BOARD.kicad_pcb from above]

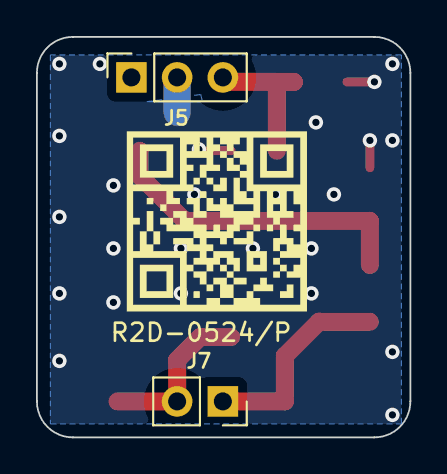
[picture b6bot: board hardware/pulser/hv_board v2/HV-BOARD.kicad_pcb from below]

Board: 2 copper layers, 20.7 x 22.2 mm, 8 parts (2 on the bottom side), 5 nets.

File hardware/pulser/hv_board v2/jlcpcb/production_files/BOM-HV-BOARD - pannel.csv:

Comment,Designator,Footprint,LCSC,Quantity
1uF,C12,C_1206_3216Metric,,1
4.7uF,C11,C_1206_3216Metric,,1
6.8uH,L1,L_1206_3216Metric,,1
1uF,C13,C_1206_3216Metric,,1
4.7uF,C10,C_1206_3216Metric,,1
IAS0105D24,B1,IAS0105D24,,1
Conn_01x03_Socket,J5,PinSocket_1x03_P2.54mm_Vertical,,1
Conn_01x02_Socket,J7,PinSocket_1x02_P2.54mm_Vertical,,1
NPTH,KiKit_MB_7_4,NPTH,,1
NPTH,KiKit_MB_3_2,NPTH,,1
NPTH,KiKit_MB_25_1,NPTH,,1
NPTH,KiKit_MB_16_3,NPTH,,1
NPTH,KiKit_MB_30_4,NPTH,,1
NPTH,KiKit_MB_16_2,NPTH,,1
NPTH,KiKit_MB_3_1,NPTH,,1
NPTH,KiKit_MB_31_2,NPTH,,1
NPTH,KiKit_MB_10_4,NPTH,,1
NPTH,KiKit_MB_30_3,NPTH,,1
NPTH,KiKit_MB_4_3,NPTH,,1
NPTH,KiKit_MB_12_3,NPTH,,1
NPTH,KiKit_MB_26_3,NPTH,,1
NPTH,KiKit_MB_29_2,NPTH,,1
NPTH,KiKit_MB_6_3,NPTH,,1
NPTH,KiKit_MB_17_1,NPTH,,1
NPTH,KiKit_MB_3_3,NPTH,,1
NPTH,KiKit_MB_24_3,NPTH,,1
NPTH,KiKit_MB_11_4,NPTH,,1
NPTH,KiKit_MB_25_4,NPTH,,1
NPTH,KiKit_MB_18_1,NPTH,,1
NPTH,KiKit_MB_25_2,NPTH,,1
NPTH,KiKit_MB_29_4,NPTH,,1
NPTH,KiKit_MB_22_3,NPTH,,1
NPTH,KiKit_MB_4_4,NPTH,,1
NPTH,KiKit_MB_8_2,NPTH,,1
NPTH,KiKit_MB_27_1,NPTH,,1
NPTH,KiKit_MB_19_2,NPTH,,1
NPTH,KiKit_MB_27_3,NPTH,,1
NPTH,KiKit_MB_24_1,NPTH,,1
NPTH,KiKit_MB_21_1,NPTH,,1
NPTH,KiKit_MB_14_1,NPTH,,1
NPTH,KiKit_MB_19_1,NPTH,,1
NPTH,KiKit_MB_8_3,NPTH,,1
NPTH,KiKit_MB_15_2,NPTH,,1
NPTH,KiKit_MB_11_3,NPTH,,1
NPTH,KiKit_MB_5_4,NPTH,,1
NPTH,KiKit_MB_19_4,NPTH,,1
NPTH,KiKit_MB_23_2,NPTH,,1
NPTH,KiKit_MB_29_1,NPTH,,1
NPTH,KiKit_MB_4_1,NPTH,,1
NPTH,KiKit_MB_24_4,NPTH,,1
NPTH,KiKit_MB_1_4,NPTH,,1
NPTH,KiKit_MB_20_4,NPTH,,1
NPTH,KiKit_MB_31_1,NPTH,,1
NPTH,KiKit_MB_13_4,NPTH,,1
NPTH,KiKit_MB_1_3,NPTH,,1
NPTH,KiKit_MB_23_1,NPTH,,1
NPTH,KiKit_MB_10_2,NPTH,,1
NPTH,KiKit_MB_11_2,NPTH,,1
NPTH,KiKit_MB_14_2,NPTH,,1
NPTH,KiKit_MB_30_2,NPTH,,1
NPTH,KiKit_MB_14_4,NPTH,,1
NPTH,KiKit_MB_16_1,NPTH,,1
NPTH,KiKit_MB_9_1,NPTH,,1
NPTH,KiKit_MB_22_1,NPTH,,1
NPTH,KiKit_MB_7_2,NPTH,,1
NPTH,KiKit_MB_8_4,NPTH,,1
NPTH,KiKit_MB_28_3,NPTH,,1
NPTH,KiKit_MB_10_1,NPTH,,1
NPTH,KiKit_MB_9_4,NPTH,,1
NPTH,KiKit_MB_17_2,NPTH,,1
NPTH,KiKit_MB_2_3,NPTH,,1
NPTH,KiKit_MB_21_3,NPTH,,1
NPTH,KiKit_MB_17_3,NPTH,,1
NPTH,KiKit_MB_7_1,NPTH,,1
NPTH,KiKit_MB_5_2,NPTH,,1
NPTH,KiKit_MB_15_3,NPTH,,1
NPTH,KiKit_MB_10_3,NPTH,,1
NPTH,KiKit_MB_20_2,NPTH,,1
NPTH,KiKit_MB_31_4,NPTH,,1
NPTH,KiKit_MB_1_2,NPTH,,1
NPTH,KiKit_MB_22_4,NPTH,,1
NPTH,KiKit_MB_31_3,NPTH,,1
NPTH,KiKit_MB_27_2,NPTH,,1
Fiducial,KiKit_FID_T_2,Fiducial,,1
NPTH,KiKit_MB_2_4,NPTH,,1
NPTH,KiKit_MB_7_3,NPTH,,1
NPTH,KiKit_MB_13_2,NPTH,,1
NPTH,KiKit_MB_15_1,NPTH,,1
NPTH,KiKit_MB_5_3,NPTH,,1
NPTH,KiKit_MB_12_1,NPTH,,1
NPTH,KiKit_MB_32_4,NPTH,,1
NPTH,KiKit_MB_1_1,NPTH,,1
NPTH,KiKit_MB_3_4,NPTH,,1
NPTH,KiKit_MB_12_4,NPTH,,1
NPTH,KiKit_MB_26_4,NPTH,,1
NPTH,KiKit_MB_21_4,NPTH,,1
NPTH,KiKit_MB_32_1,NPTH,,1
Fiducial,KiKit_FID_T_1,Fiducial,,1
NPTH,KiKit_MB_27_4,NPTH,,1
NPTH,KiKit_MB_18_3,NPTH,,1
NPTH,KiKit_MB_29_3,NPTH,,1
NPTH,KiKit_MB_30_1,NPTH,,1
NPTH,KiKit_MB_20_1,NPTH,,1
NPTH,KiKit_MB_19_3,NPTH,,1
NPTH,KiKit_MB_5_1,NPTH,,1
NPTH,KiKit_MB_11_1,NPTH,,1
NPTH,KiKit_MB_28_1,NPTH,,1
NPTH,KiKit_MB_22_2,NPTH,,1
NPTH,KiKit_MB_26_2,NPTH,,1
NPTH,KiKit_MB_4_2,NPTH,,1
NPTH,KiKit_MB_9_3,NPTH,,1
NPTH,KiKit_MB_6_4,NPTH,,1
NPTH,KiKit_MB_13_3,NPTH,,1
NPTH,KiKit_MB_32_2,NPTH,,1
NPTH,KiKit_MB_15_4,NPTH,,1
NPTH,KiKit_MB_26_1,NPTH,,1
NPTH,KiKit_MB_13_1,NPTH,,1
NPTH,KiKit_MB_2_2,NPTH,,1
NPTH,KiKit_MB_17_4,NPTH,,1
NPTH,KiKit_MB_9_2,NPTH,,1
NPTH,KiKit_MB_14_3,NPTH,,1
NPTH,KiKit_MB_24_2,NPTH,,1
NPTH,KiKit_MB_6_2,NPTH,,1
NPTH,KiKit_MB_6_1,NPTH,,1
NPTH,KiKit_MB_2_1,NPTH,,1
NPTH,KiKit_MB_32_3,NPTH,,1
NPTH,KiKit_MB_16_4,NPTH,,1
NPTH,KiKit_MB_28_4,NPTH,,1
NPTH,KiKit_MB_20_3,NPTH,,1
NPTH,KiKit_MB_12_2,NPTH,,1
NPTH,KiKit_MB_8_1,NPTH,,1
NPTH,KiKit_MB_18_4,NPTH,,1
NPTH,KiKit_MB_18_2,NPTH,,1
NPTH,KiKit_MB_25_3,NPTH,,1
NPTH,KiKit_MB_28_2,NPTH,,1
NPTH,KiKit_MB_23_3,NPTH,,1
Fiducial,KiKit_FID_T_3,Fiducial,,1
NPTH,KiKit_MB_21_2,NPTH,,1
NPTH,KiKit_MB_23_4,NPTH,,1
Fiducial,KiKit_FID_B_1,Fiducial,,1
Fiducial,KiKit_FID_B_2,Fiducial,,1
Fiducial,KiKit_FID_B_3,Fiducial,,1
